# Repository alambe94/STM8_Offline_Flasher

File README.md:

STM8S003 offline flasher

# STM8_Flasher

https://sourceforge.net/projects/stm32f100tostm8s105swimlibrary/

https://github.com/versaloon/versaloon

https://github.com/cole3/STM8_SWIM

https://github.com/dimitarm1/SWIM_Programmer

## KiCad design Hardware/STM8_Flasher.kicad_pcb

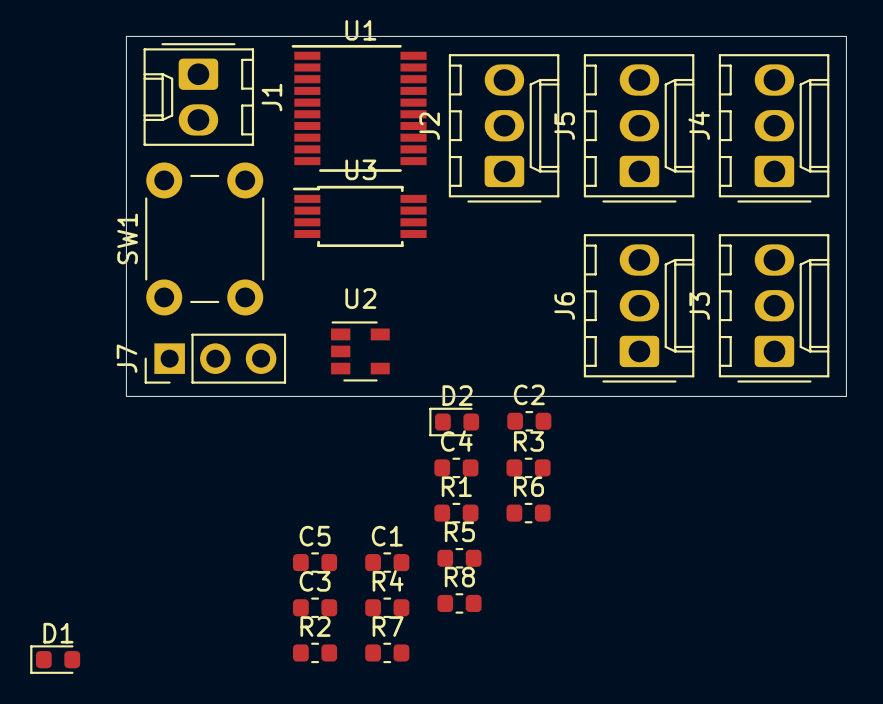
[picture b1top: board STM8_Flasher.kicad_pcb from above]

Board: 2 copper layers, 40.0 x 20.0 mm, 26 parts (0 on the bottom side), 24 nets, no tracks yet.

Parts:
C1, C2, C3, C5: 1u; C_0603_1608Metric
C4: 10n; C_0603_1608Metric
D1: RED_LED; LED_0603_1608Metric
D2: GREEN_LED; LED_0603_1608Metric
J1: PWR; Molex_KK-254_AE-6410-02A_1x02_P2.54mm_Vertical
J2: SWIM_PORT1; Molex_KK-254_AE-6410-03A_1x03_P2.54mm_Vertical
J3: SWIM_PORT2; Molex_KK-254_AE-6410-03A_1x03_P2.54mm_Vertical
J4: SWIM_PORT3; Molex_KK-254_AE-6410-03A_1x03_P2.54mm_Vertical
J5: SWIM_PORT4; Molex_KK-254_AE-6410-03A_1x03_P2.54mm_Vertical
J6: SWIM_PORT5; Molex_KK-254_AE-6410-03A_1x03_P2.54mm_Vertical
J7: ISP; PinHeader_1x03_P2.54mm_Vertical
R1: 10k; R_0603_1608Metric
R2, R3: 1k; R_0603_1608Metric
R4, R5, R6, R7, R8: 3.3k; R_0603_1608Metric
SW1: PROG_SW; SW_PUSH_6mm
U1: STM8S003F3P; TSSOP-20_4.4x6.5mm_P0.65mm
U2: MIC5205-3.3YM5; SOT-23-5
U3: 24LC256; TSSOP-8_4.4x3mm_P0.65mm

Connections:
GND: C1.2, C2.2, C3.2, C4.2, C5.2, J1.2, J2.3, J3.3, J4.3, J5.3, J6.3, J7.3, SW1.1, U1.7, U3.1, U3.2, U3.4, U3.7
I2C_SCL: U1.12, U3.6
I2C_SDA: U1.11, U3.5
MCU_3.3V: C5.1, R1.1, R2.1, R3.1, R4.1, R5.1, R6.1, R7.1, R8.1, U1.9, U2.5, U3.8
NRST: C1.1, J7.2, U1.4
unnamed: C2.1, U1.8
unnamed: C3.1, J1.1, U2.1, U2.3
unnamed: C4.1, U2.4
unnamed: D1.2, R2.2
unnamed: D2.2, R3.2
PROG_SW: R1.2, SW1.2, U1.10
READ_LED: D1.1, U1.5
SWIM: J7.1, U1.18
SWIM_NRST1: J2.2, U1.13
SWIM_NRST2: J3.2, U1.14
SWIM_NRST3: J4.2, U1.15
SWIM_NRST4: J5.2, U1.16
SWIM_NRST5: J6.2, U1.17
SWIM_PORT1: J2.1, R4.2, U1.19
SWIM_PORT2: J3.1, R5.2, U1.20
SWIM_PORT3: J4.1, R6.2, U1.1
SWIM_PORT4: J5.1, R7.2, U1.2
SWIM_PORT5: J6.1, R8.2, U1.3
WRITE _LED: D2.1, U1.6

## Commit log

2017-10-04 using PWM HW instead of SPI
2019-02-21 gpio bit banging
2019-02-23 using interrupt to capture SWIM in data
2019-02-23 reading and writing working
2019-02-23 main.c restored
2019-02-23 main
2019-02-23 screenshot renamed
2019-02-25 for loop unrolled for speed
2019-02-25 schematic update
2019-02-25 reading AT24C
2019-02-25 AT24C reading
2019-02-26 using soft i2c driver
2019-02-26 AT24 driver update
2019-02-27 schematic added
2019-02-27 unlock optionbyte fixed
2019-02-27 kicad stm8.lib added
2019-08-16 using reset routine
2019-08-30 trying to implement multi flasher
2019-08-31 write multiple, read single
2019-08-31 git ignore
2019-08-31 device specific code
2019-08-31 stdlib update
2019-08-31 adding test code
2019-08-31 updte
2019-08-31 stvd cosmic
2019-09-03 eop fixed, update
2019-09-03 iterating gpios
2019-09-05 iterating gpios for loop fixed
2019-09-05 tests
2019-09-06 iterating gpios for loop update
2019-09-14 at24cxx update
2019-09-14 pin 6 removed
2019-10-17 new schematic
2020-03-24 clean
